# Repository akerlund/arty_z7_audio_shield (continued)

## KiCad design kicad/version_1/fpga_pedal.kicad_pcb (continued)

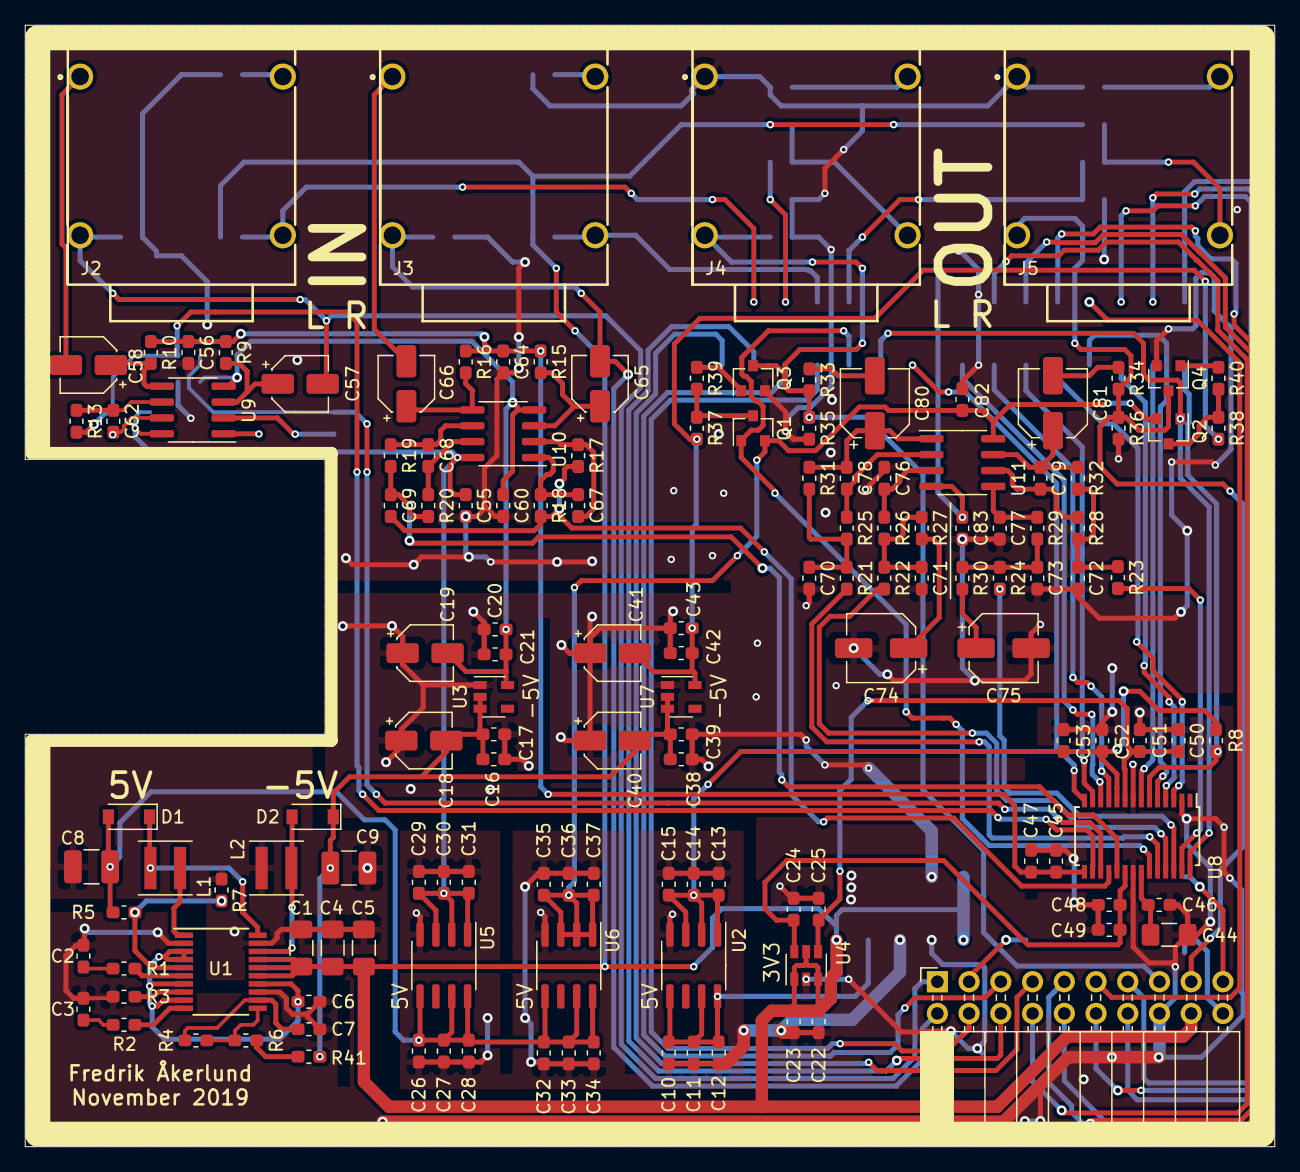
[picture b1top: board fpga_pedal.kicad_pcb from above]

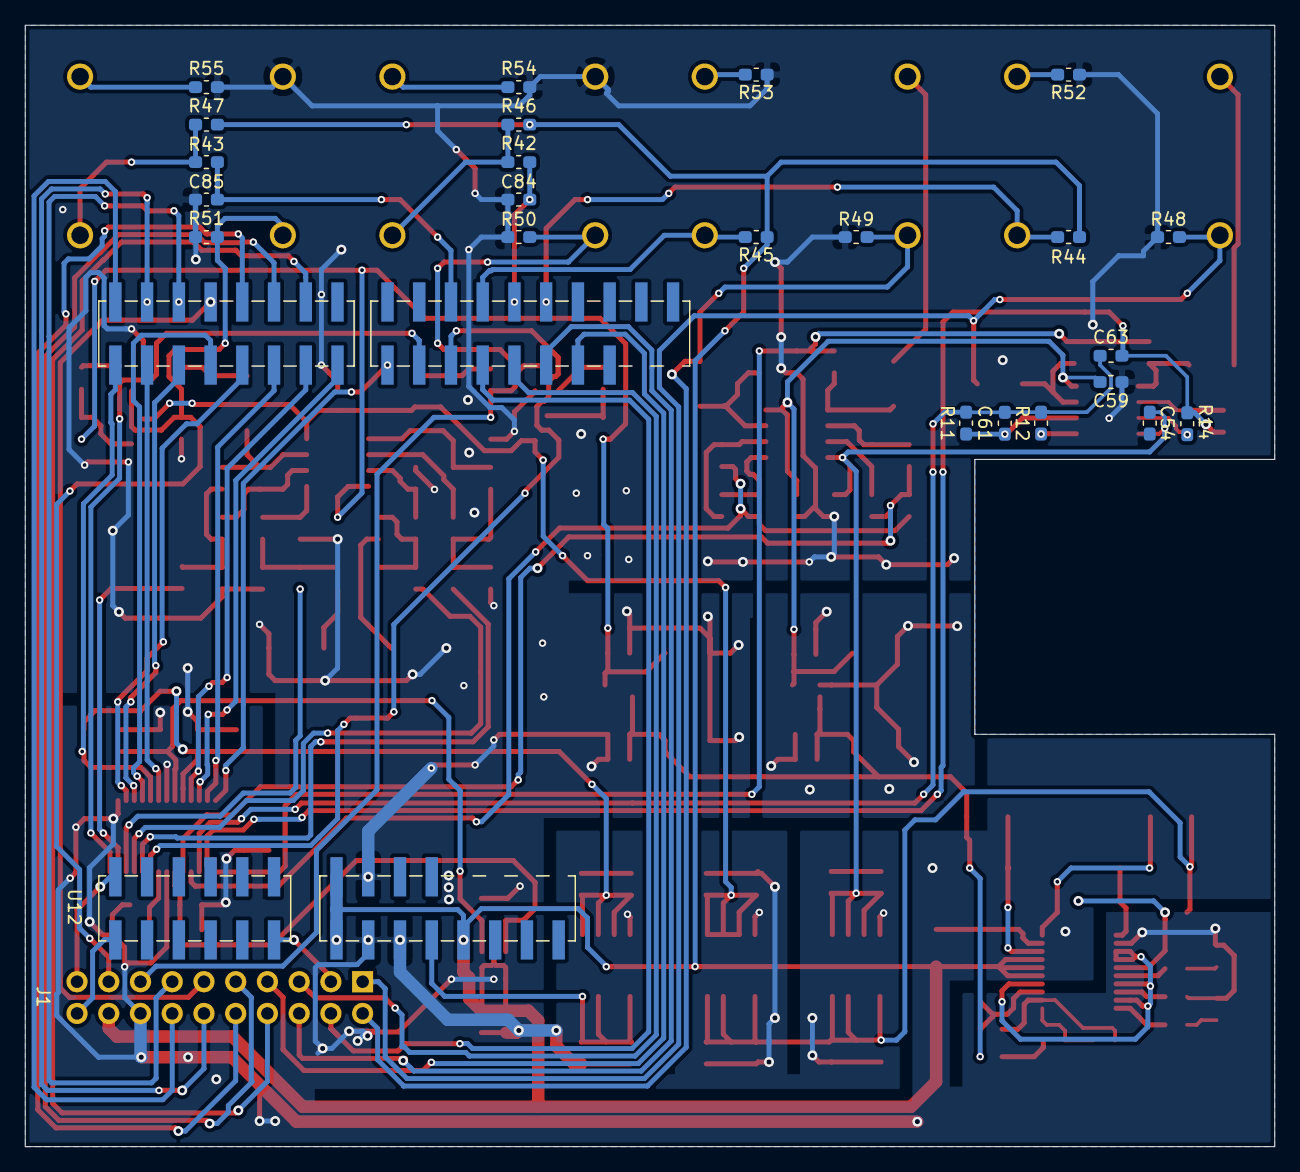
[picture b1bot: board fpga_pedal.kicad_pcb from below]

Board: 2 copper layers, 100.0 x 89.8 mm, 165 parts (23 on the bottom side), 106 nets.

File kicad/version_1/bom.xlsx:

Ref | Qnty |  | Value | Part | Footprint | Description | Vendor
C1, C4 | 2 |  | 3.3uF | Device:C | Capacitor_SMD:C_0603_1608Metric_Pad1.05x0.95mm_HandSolder | Unpolarized capacitor
C2, C3 | 2 |  | 47nF | Device:C | Capacitor_SMD:C_0603_1608Metric_Pad1.05x0.95mm_HandSolder | Unpolarized capacitor
C5 | 1 |  | 5.6uF | Device:C | Capacitor_SMD:C_0603_1608Metric_Pad1.05x0.95mm_HandSolder | Unpolarized capacitor
C6, C7, C11, C14, C22, C24, C25, C27, C30, C33, C36, C45, C47, C48, C50, C53 | 16 |  | 1uF | Device:C | Capacitor_SMD:C_0603_1608Metric_Pad1.05x0.95mm_HandSolder | Unpolarized capacitor
C8, C9 | 2 |  | 10uF | Device:C | Capacitor_SMD:C_1210_3225Metric_Pad1.42x2.65mm_HandSolder | Unpolarized capacitor
C10, C13, C16, C21, C23, C26, C29, C32, C35, C38, C43 | 11 |  | 100nF | Device:C | Capacitor_SMD:C_0603_1608Metric_Pad1.05x0.95mm_HandSolder | Unpolarized capacitor
C12, C15, C28, C31, C34, C37 | 6 |  | 2.2uF | Device:C | Capacitor_SMD:C_0603_1608Metric_Pad1.05x0.95mm_HandSolder | Unpolarized capacitor
C17, C20, C39, C42 | 4 |  | 1nF | Device:C | Capacitor_SMD:C_0603_1608Metric_Pad1.05x0.95mm_HandSolder | Unpolarized capacitor
C18, C19, C40, C41 | 4 |  | 2.2uF | Device:CP_Small | Capacitor_SMD:CP_Elec_4x5.7 | Polarized capacitor, small symbol
C44 | 1 |  | 47uF | Device:C | Capacitor_SMD:C_1206_3216Metric_Pad1.42x1.75mm_HandSolder | Unpolarized capacitor
C46, C49, C51, C52 | 4 |  | 0.1uF | Device:C | Capacitor_SMD:C_0603_1608Metric_Pad1.05x0.95mm_HandSolder | Unpolarized capacitor
C54, C55, C59, C60, C82, C83 | 6 |  | 2.2uF | Device:C | Capacitor_SMD:C_0603_1608Metric_Pad1.05x0.95mm_HandSolder | Unpolarized capacitor
C56, C64 | 2 | C0G | 0.01uF | Device:C | Capacitor_SMD:C_0603_1608Metric_Pad1.05x0.95mm_HandSolder | Unpolarized capacitor
C57, C58, C65, C66 | 4 |  | 10uF | Device:CP_Small | Capacitor_SMD:CP_Elec_4x5.7 | Polarized capacitor, small symbol
C61, C62, C67, C68, C78, C79 | 6 | C0G | 470pF | Device:C | Capacitor_SMD:C_0603_1608Metric_Pad1.05x0.95mm_HandSolder | Unpolarized capacitor
C63, C69 | 2 | C0G | 2.7nF | Device:C | Capacitor_SMD:C_0603_1608Metric_Pad1.05x0.95mm_HandSolder | Unpolarized capacitor
C70, C72 | 2 | C0G | 2.2nF | Device:C | Capacitor_SMD:C_0603_1608Metric_Pad1.05x0.95mm_HandSolder | Unpolarized capacitor
C71, C73 | 2 | C0G | 6.8nF | Device:C | Capacitor_SMD:C_0603_1608Metric_Pad1.05x0.95mm_HandSolder | Unpolarized capacitor
C74, C75 | 2 |  | 22uF | Device:C | Capacitor_SMD:CP_Elec_5x5.7 | Unpolarized capacitor
C76, C77 | 2 | C0G | 1.5nF | Device:C | Capacitor_SMD:C_0603_1608Metric_Pad1.05x0.95mm_HandSolder | Unpolarized capacitor
C80, C81 | 2 |  | 22uF | Device:CP_Small | Capacitor_SMD:CP_Elec_5x5.7 | Polarized capacitor, small symbol
D1, D2 | 2 |  | SCH | Device:D_Schottky | Diode_SMD:D_SOD-123 | Schottky diode
J1 | 1 |  | Conn_02x10_Odd_Even | Connector_Generic:Conn_02x10_Odd_Even | Connector_PinSocket_2.54mm:PinSocket_2x10_P2.54mm_Horizontal | Generic connector, double row, 02x10, odd/even pin numbering scheme (row 1 odd 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
J2 | 1 |  | IN_LEFT | SamacSys_Parts:NMJ4HCD2 | SamacSys_Parts:NMJ4HCD2 | Phone Connectors 2C MONO 2-SPST NC
J3 | 1 |  | OUT_LEFT | SamacSys_Parts:NMJ4HCD2 | SamacSys_Parts:NMJ4HCD2 | Phone Connectors 2C MONO 2-SPST NC
J4 | 1 |  | IN_RIGHT | SamacSys_Parts:NMJ4HCD2 | SamacSys_Parts:NMJ4HCD2 | Phone Connectors 2C MONO 2-SPST NC
J5 | 1 |  | OUT_RIGHT | SamacSys_Parts:NMJ4HCD2 | SamacSys_Parts:NMJ4HCD2 | Phone Connectors 2C MONO 2-SPST NC
L1 | 1 |  | 2.2uH | Device:L_Small | Inductor_SMD:L_Coilcraft_XxL4020 | Inductor, small symbol
L2 | 1 |  | 3.3uH | Device:L_Small | Inductor_SMD:L_Coilcraft_XxL4030 | Inductor, small symbol
Q1, Q2, Q3, Q4 | 4 |  | PNP_BEC | Device:Q_PNP_BEC | Package_TO_SOT_SMD:SOT-23 | PNP transistor, base/emitter/collector
R1 | 1 |  | 4.7k | Device:R | Resistor_SMD:R_0603_1608Metric_Pad1.05x0.95mm_HandSolder | Resistor
R2 | 1 |  | 8.2k | Device:R | Resistor_SMD:R_0603_1608Metric_Pad1.05x0.95mm_HandSolder | Resistor
R3 | 1 |  | 268k | Device:R | Resistor_SMD:R_0603_1608Metric_Pad1.05x0.95mm_HandSolder | Resistor
R4 | 1 |  | 158k | Device:R | Resistor_SMD:R_0603_1608Metric_Pad1.05x0.95mm_HandSolder | Resistor
R5 | 1 |  | 604k | Device:R | Resistor_SMD:R_0603_1608Metric_Pad1.05x0.95mm_HandSolder | Resistor
R6 | 1 |  | 1.15M | Device:R | Resistor_SMD:R_0603_1608Metric_Pad1.05x0.95mm_HandSolder | Resistor
R7 | 1 |  | 115k | Device:R | Resistor_SMD:R_0603_1608Metric_Pad1.05x0.95mm_HandSolder | Resistor
R8, R35, R36 | 3 |  | 47k | Device:R | Resistor_SMD:R_0603_1608Metric_Pad1.05x0.95mm_HandSolder | Resistor
R9, R10, R15, R16, R37, R38 | 6 |  | 10k | Device:R | Resistor_SMD:R_0603_1608Metric_Pad1.05x0.95mm_HandSolder | Resistor
R11, R13, R17, R19 | 4 |  | 634R | Device:R | Resistor_SMD:R_0603_1608Metric_Pad1.05x0.95mm_HandSolder | Resistor
R12, R14, R18, R20 | 4 |  | 91R | Device:R | Resistor_SMD:R_0603_1608Metric_Pad1.05x0.95mm_HandSolder | Resistor
R21, R23 | 2 |  | 4.42k | Device:R | Resistor_SMD:R_0603_1608Metric_Pad1.05x0.95mm_HandSolder | Resistor
R22, R24 | 2 |  | 1.33k | Device:R | Resistor_SMD:R_0603_1608Metric_Pad1.05x0.95mm_HandSolder | Resistor
R25, R28 | 2 |  | 2.32k | Device:R | Resistor_SMD:R_0603_1608Metric_Pad1.05x0.95mm_HandSolder | Resistor
R26, R29 | 2 |  | 715R | Device:R | Resistor_SMD:R_0603_1608Metric_Pad1.05x0.95mm_HandSolder | Resistor
R27, R30 | 2 |  | 1.5k | Device:R | Resistor_SMD:R_0603_1608Metric_Pad1.05x0.95mm_HandSolder | Resistor
R31, R32 | 2 |  | 4.99k | Device:R | Resistor_SMD:R_0603_1608Metric_Pad1.05x0.95mm_HandSolder | Resistor
R33, R34 | 2 |  | 560R | Device:R | Resistor_SMD:R_0603_1608Metric_Pad1.05x0.95mm_HandSolder | Resistor
R39, R40 | 2 |  | 2k | Device:R | Resistor_SMD:R_0603_1608Metric_Pad1.05x0.95mm_HandSolder | Resistor
U1 | 1 |  | ADP5071 | freakuency:ADP5071 | Package_SO:TSSOP-20_4.4x6.5mm_P0.65mm
U2, U5, U6 | 3 |  | ADP7118 | freakuency:ADP7118 | Package_SO:SOIC-8_3.9x4.9mm_P1.27mm
U3, U7 | 2 |  | ADP7182 | freakuency:ADP7182 | Package_TO_SOT_SMD:SOT-23-5
U4 | 1 |  | MIC5211 | freakuency:MIC5211 | Package_TO_SOT_SMD:SOT-23-6
U8 | 1 |  | CS4272 | freakuency:CS4272 | Package_SO:TSSOP-28_4.4x9.7mm_P0.65mm
U9, U10, U11 | 3 |  | MC33078 | freakuency:MC33078 | Package_SO:SOIC-8_3.9x4.9mm_P1.27mm
U12 | 1 |  | chip_kit | freakuency:chip_kit | f_library:chipKIT

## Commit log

2019-12-27 Upload version 1 of the PCB
